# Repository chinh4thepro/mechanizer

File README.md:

## What and Why?

This is an ortholinear, split keyboard with wireless functionality and a display with a theme based on the song Mesmerizer by 32ki. I designed this keyboard to improve on issues I had with my previous ortholinear keyboard design, the blahajergo.

## Images

### Overall

### Schematic

### PCB

## BOM

| Name                                      | Qty   | Price     | Vendor        | Link                                                                              |
|-------------------------------------------|-------|-----------|---------------|-----------------------------------------------------------------------------------|
| THT 1N4148 Diodes                         | 54    | $0.00     | HackClub      | N/A                                                                               |
| KBDiy Toy                                 | 54    | $24.45    | AliExpress    | https://www.aliexpress.us/item/3256807300360436.html                              |
| JWK Linear Switches                       | 54    | $14.4     | typeractive   | https://typeractive.xyz/products/jwk-jwick-linear-switches?variant=45434593968359 |
| Kalih MX hotswap sockets                  | 54    | $13.45    | AliExpress    | https://www.aliexpress.us/item/3256808768257055.html                              |
| 4P4C jack                                 | 2     | $1.87     | AliExpress    | https://www.aliexpress.us/item/3256807699240291.html                              |
| JST connector                             | 2     | $0.73     | AliExpress    | https://www.aliexpress.us/item/3256808844534562.html                              |
| 0.91" Oled display                        | 2     | $1.96     | AliExpress    | https://www.aliexpress.us/item/3256805114690528.html                              |
| 3.7v Lithium battery                      | 2     | $8.00     | typeractive   | https://typeractive.xyz/products/lithium-battery-110mah?variant=43294731665639    |
| JST connector                             | 2     | $1.00     | typeractive   | https://typeractive.xyz/products/battery-jack?variant=45597492707559              |
| SMD side button                           | 2     | $1.50     | typeractive   | https://typeractive.xyz/products/reset-button                                     |
| SPDT Switch                               | 2     | $1.50     | typeractive   | https://typeractive.xyz/products/power-switch?variant=45597854171367              |
| M2 screws                                 | 24    | $2.44     | AliExpress    | https://www.aliexpress.us/item/2255799870438450.html                              |
| M2 standoffs                              | 12    | $5.40     | AliExpress    | https://www.aliexpress.us/item/3256806016664762.html                              |
| Seeed XIAO ESP32-S3 Plus (already own)    | 2     | $13.80    | seeedstudio   | https://www.seeedstudio.com/Seeed-Studio-XIAO-ESP32S3-Plus-p-6361.html            |
| PCB                                       | 1 (5) | $36.92    | jlcpcb        | See jlcpcb pic in Files                                                           |

| Total                                                                                                                                             |
|---------------------------------------------------------------------------------------------------------------------------------------------------|
| AliExpress: $52.83 subtotal + $4.24 shipping + $3.33 fees = $58.61 total                                                                          |
| typeractive: $26.40 subtotal + $0.00 shipping + $0.00 fees = $26.40 total                                                                         |
| seeedstudio: $0.00 subtotal + $0.00 shipping + $0.00 fees = $0.00 total                                                                           |
| jlcpcb: $21.40 subtotal + $15.52 shipping + $0.00 fees = $36.92 total                                                                             |
| Total: $121.93                                                                                                                                     |

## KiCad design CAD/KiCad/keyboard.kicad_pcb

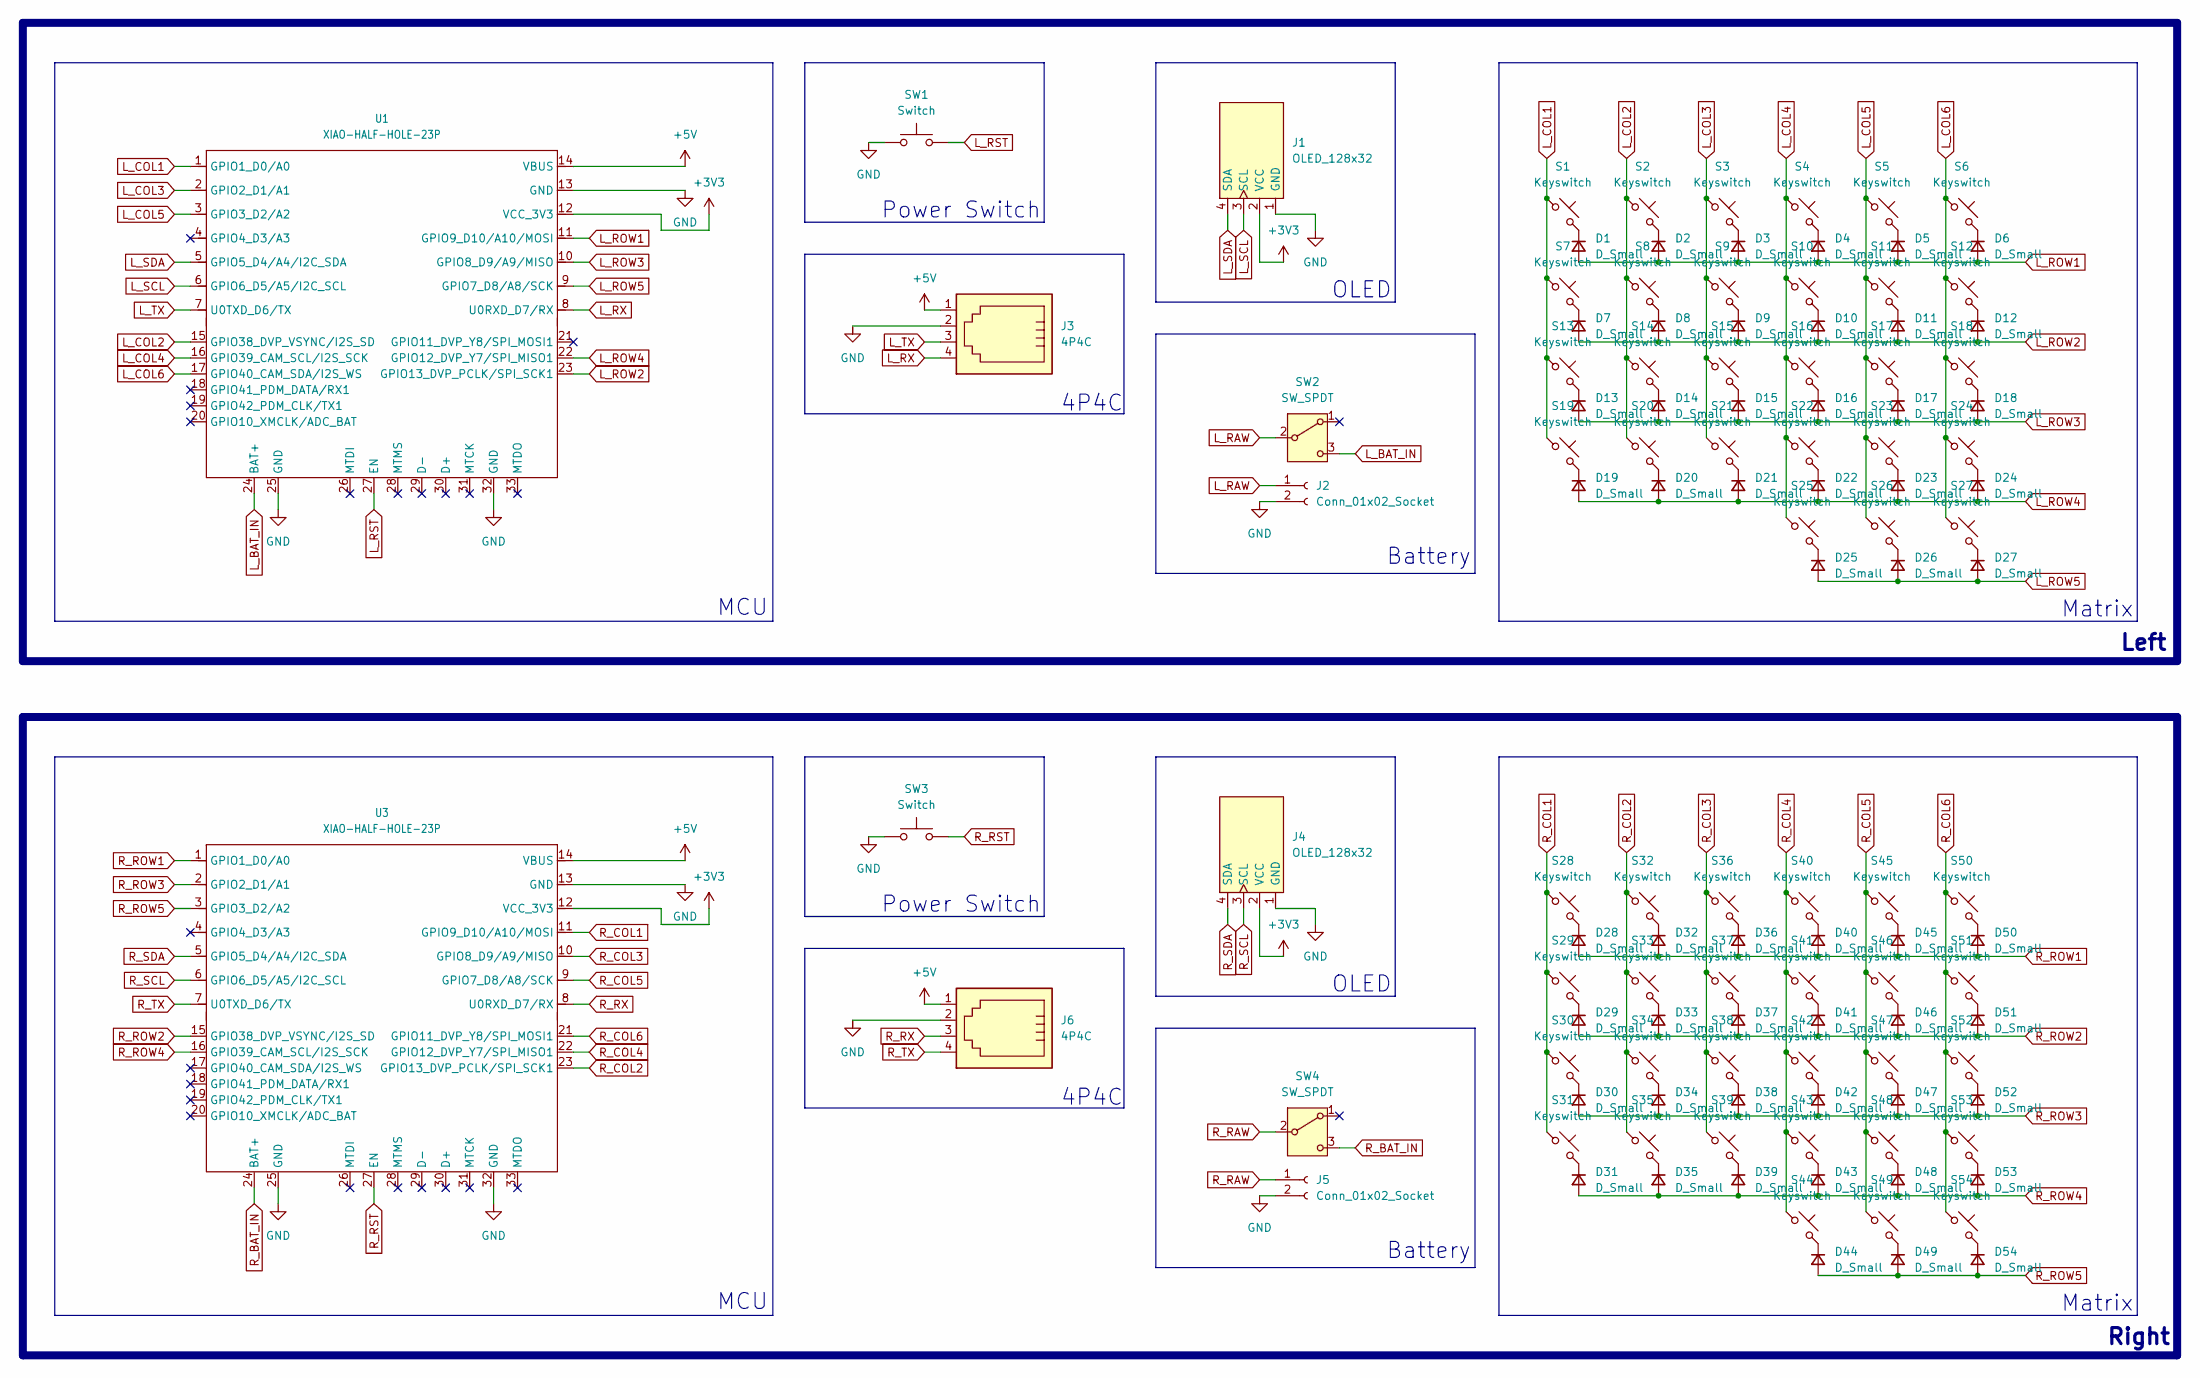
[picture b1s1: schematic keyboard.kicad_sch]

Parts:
D1, D2, D3, D4, D5, D6, D7, D8, D9, D10, D11, D12, D13, D14, D15, D16, D17, D18, D19, D20, D21, D22, D23, D24, D25, D26, D27, D28, D29, D30, D31, D32, D33, D34, D35, D36, D37, D38, D39, D40, D41, D42, D43, D44, D45, D46, D47, D48, D49, D50, D51, D52, D53, D54: D_Small; ComboDiode
J1, J4: OLED_128x32
J2, J5: Conn_01x02_Socket; JST_PH_S2B-PH-K_1x02_P2.00mm_Horizontal
J3, J6: 4P4C; RJ9_Evercom_5301-440xxx_Horizontal
S1, S2, S3, S4, S5, S6, S7, S8, S9, S10, S11, S12, S13, S14, S15, S16, S17, S18, S19, S20, S21, S22, S23, S24, S25, S26, S27, S28, S29, S30, S31, S32, S33, S34, S35, S36, S37, S38, S39, S40, S41, S42, S43, S44, S45, S46, S47, S48, S49, S50, S51, S52, S53, S54: Keyswitch; Hotswap_MX
SW1, SW3: Switch; reset_switch_smd_side
SW2, SW4: SW_SPDT; power_switch_smd_side
U1, U3: XIAO-HALF-HOLE-23P; Xiao_ESP32S3_Plus.kicad_sym

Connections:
+3V3: J1.2 (VCC), J4.2 (VCC), U1.12 (VCC_3V3), U3.12 (VCC_3V3)
+5V: J3.1, J6.1, U1.14 (VBUS), U3.14 (VBUS)
GND: J1.1 (GND), J2.2, J3.2, J4.1 (GND), J5.2, J6.2, SW1.1, SW3.1, U1.13 (GND), U1.25 (GND), U1.32 (GND), U3.13 (GND), U3.25 (GND), U3.32 (GND)
L_BAT_IN: SW2.3 (C), U1.24 (BAT+)
L_COL1: S1.1, S7.1, S13.1, S19.1, U1.1 (GPIO1_D0/A0)
L_COL2: S2.1, S8.1, S14.1, S20.1, U1.15 (GPIO38_DVP_VSYNC/I2S_SD)
L_COL3: S3.1, S9.1, S15.1, S21.1, U1.2 (GPIO2_D1/A1)
L_COL4: S4.1, S10.1, S16.1, S22.1, S25.1, U1.16 (GPIO39_CAM_SCL/I2S_SCK)
L_COL5: S5.1, S11.1, S17.1, S23.1, S26.1, U1.3 (GPIO3_D2/A2)
L_COL6: S6.1, S12.1, S18.1, S24.1, S27.1, U1.17 (GPIO40_CAM_SDA/I2S_WS)
L_RAW: J2.1, SW2.2 (B)
L_ROW1: D1.2 (A), D2.2 (A), D3.2 (A), D4.2 (A), D5.2 (A), D6.2 (A), U1.11 (GPIO9_D10/A10/MOSI)
L_ROW2: D7.2 (A), D8.2 (A), D9.2 (A), D10.2 (A), D11.2 (A), D12.2 (A), U1.23 (GPIO13_DVP_PCLK/SPI_SCK1)
L_ROW3: D13.2 (A), D14.2 (A), D15.2 (A), D16.2 (A), D17.2 (A), D18.2 (A), U1.10 (GPIO8_D9/A9/MISO)
L_ROW4: D19.2 (A), D20.2 (A), D21.2 (A), D22.2 (A), D23.2 (A), D24.2 (A), U1.22 (GPIO12_DVP_Y7/SPI_MISO1)
L_ROW5: D25.2 (A), D26.2 (A), D27.2 (A), U1.9 (GPIO7_D8/A8/SCK)
L_RST: SW1.2, U1.27 (EN)
L_RX: J3.4, U1.8 (U0RXD_D7/RX)
L_SCL: J1.3 (SCL), U1.6 (GPIO6_D5/A5/I2C_SCL)
L_SDA: J1.4 (SDA), U1.5 (GPIO5_D4/A4/I2C_SDA)
L_TX: J3.3, U1.7 (U0TXD_D6/TX)
unnamed: D1.1 (K), S1.2
unnamed: D2.1 (K), S2.2
unnamed: D3.1 (K), S3.2
unnamed: D4.1 (K), S4.2
unnamed: D5.1 (K), S5.2
unnamed: D6.1 (K), S6.2
unnamed: D7.1 (K), S7.2
unnamed: D8.1 (K), S8.2
unnamed: D9.1 (K), S9.2
unnamed: D10.1 (K), S10.2
unnamed: D11.1 (K), S11.2
unnamed: D12.1 (K), S12.2
unnamed: D13.1 (K), S13.2
unnamed: D14.1 (K), S14.2
unnamed: D15.1 (K), S15.2
unnamed: D16.1 (K), S16.2
unnamed: D17.1 (K), S17.2
unnamed: D18.1 (K), S18.2
unnamed: D19.1 (K), S19.2
unnamed: D20.1 (K), S20.2
unnamed: D21.1 (K), S21.2
unnamed: D22.1 (K), S22.2
unnamed: D23.1 (K), S23.2
unnamed: D24.1 (K), S24.2
unnamed: D25.1 (K), S25.2
unnamed: D26.1 (K), S26.2
unnamed: D27.1 (K), S27.2
unnamed: D28.1 (K), S28.2
unnamed: D29.1 (K), S29.2
unnamed: D30.1 (K), S30.2
unnamed: D31.1 (K), S31.2
unnamed: D32.1 (K), S32.2
unnamed: D33.1 (K), S33.2
unnamed: D34.1 (K), S34.2
unnamed: D35.1 (K), S35.2
unnamed: D36.1 (K), S36.2
unnamed: D37.1 (K), S37.2
unnamed: D38.1 (K), S38.2
unnamed: D39.1 (K), S39.2
unnamed: D40.1 (K), S40.2
unnamed: D41.1 (K), S41.2
unnamed: D42.1 (K), S42.2
unnamed: D43.1 (K), S43.2
unnamed: D44.1 (K), S44.2
unnamed: D45.1 (K), S45.2
unnamed: D46.1 (K), S46.2
unnamed: D47.1 (K), S47.2
unnamed: D48.1 (K), S48.2
unnamed: D49.1 (K), S49.2
unnamed: D50.1 (K), S50.2
unnamed: D51.1 (K), S51.2
unnamed: D52.1 (K), S52.2
unnamed: D53.1 (K), S53.2
unnamed: D54.1 (K), S54.2
R_BAT_IN: SW4.3 (C), U3.24 (BAT+)
R_COL1: S28.1, S29.1, S30.1, S31.1, U3.11 (GPIO9_D10/A10/MOSI)
R_COL2: S32.1, S33.1, S34.1, S35.1, U3.23 (GPIO13_DVP_PCLK/SPI_SCK1)
R_COL3: S36.1, S37.1, S38.1, S39.1, U3.10 (GPIO8_D9/A9/MISO)
R_COL4: S40.1, S41.1, S42.1, S43.1, S44.1, U3.22 (GPIO12_DVP_Y7/SPI_MISO1)
R_COL5: S45.1, S46.1, S47.1, S48.1, S49.1, U3.9 (GPIO7_D8/A8/SCK)
R_COL6: S50.1, S51.1, S52.1, S53.1, S54.1, U3.21 (GPIO11_DVP_Y8/SPI_MOSI1)
R_RAW: J5.1, SW4.2 (B)
R_ROW1: D28.2 (A), D32.2 (A), D36.2 (A), D40.2 (A), D45.2 (A), D50.2 (A), U3.1 (GPIO1_D0/A0)
R_ROW2: D29.2 (A), D33.2 (A), D37.2 (A), D41.2 (A), D46.2 (A), D51.2 (A), U3.15 (GPIO38_DVP_VSYNC/I2S_SD)
R_ROW3: D30.2 (A), D34.2 (A), D38.2 (A), D42.2 (A), D47.2 (A), D52.2 (A), U3.2 (GPIO2_D1/A1)
R_ROW4: D31.2 (A), D35.2 (A), D39.2 (A), D43.2 (A), D48.2 (A), D53.2 (A), U3.16 (GPIO39_CAM_SCL/I2S_SCK)
R_ROW5: D44.2 (A), D49.2 (A), D54.2 (A), U3.3 (GPIO3_D2/A2)
R_RST: SW3.2, U3.27 (EN)
R_RX: J6.3, U3.8 (U0RXD_D7/RX)
R_SCL: J4.3 (SCL), U3.6 (GPIO6_D5/A5/I2C_SCL)
R_SDA: J4.4 (SDA), U3.5 (GPIO5_D4/A4/I2C_SDA)
R_TX: J6.4, U3.7 (U0TXD_D6/TX)

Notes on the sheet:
Power Switch
Left
Battery
Matrix
4P4C
Right
MCU
OLED

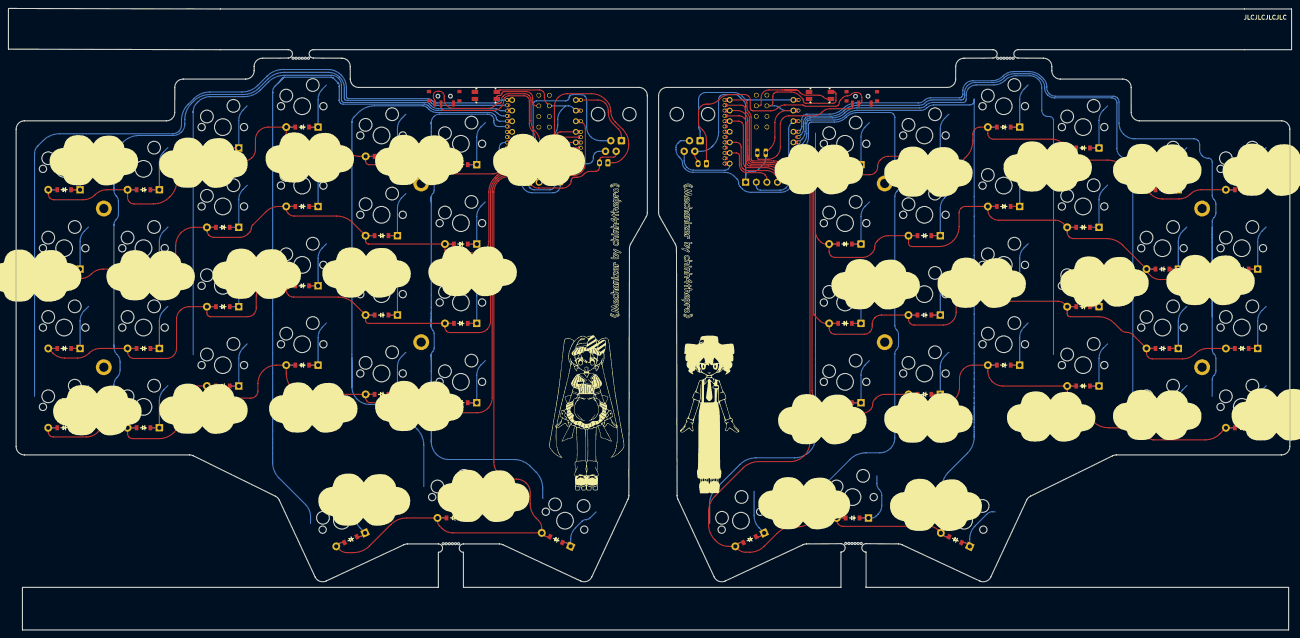
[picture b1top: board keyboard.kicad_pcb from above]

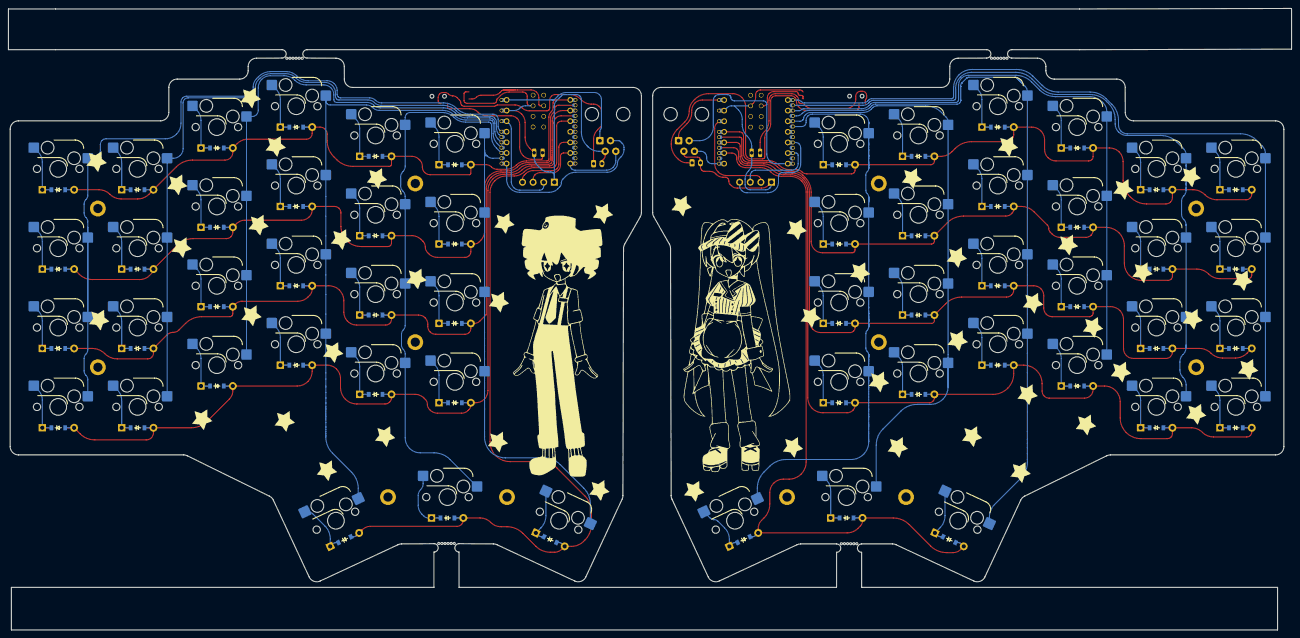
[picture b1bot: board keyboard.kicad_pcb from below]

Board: 2 copper layers, 307.2 x 148.8 mm, 132 parts (2 on the bottom side), 93 nets.

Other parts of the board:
H1, H2, H3, H4, H5, H6, H7, H8, H9, H10, H11, H12: mounting_hole_plated

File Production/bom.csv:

Designator,Footprint,Quantity,Value,LCSC Part #
"D1, D10, D11, D12, D13, D14, D15, D16, D17, D18, D19, D2, D20, D21, D22, D23, D24, D25, D26, D27, D28, D29, D3, D30, D31, D32, D33, D34, D35, D36, D37, D38, D39, D4, D40, D41, D42, D43, D44, D45, D46, D47, D48, D49, D5, D50, D51, D52, D53, D54, D6, D7, D8, D9",ComboDiode,54,D_Small,
"H1, H10, H11, H12, H2, H3, H4, H5, H6, H7, H8, H9",mounting_hole_plated,12,,
"J1, J4",OLED_128x32,2,OLED_128x32,
"J2, J5",JST_PH_S2B-PH-K_1x02_P2.00mm_Horizontal,2,Conn_01x02_Socket,
"J3, J6",RJ9_Evercom_5301-440xxx_Horizontal,2,4P4C,
"S1, S10, S11, S12, S13, S14, S15, S16, S17, S18, S19, S2, S20, S21, S22, S23, S24, S25, S26, S27, S28, S29, S3, S30, S31, S32, S33, S34, S35, S36, S37, S38, S39, S4, S40, S41, S42, S43, S44, S45, S46, S47, S48, S49, S5, S50, S51, S52, S53, S54, S6, S7, S8, S9",Hotswap_MX,54,Keyswitch,
"SW1, SW3",reset_switch_smd_side,2,Switch,
"SW2, SW4",power_switch_smd_side,2,SW_SPDT,
"U1, U3",Xiao_ESP32S3_Plus.kicad_sym,2,XIAO-HALF-HOLE-23P,

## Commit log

2025-03-02 kicad
2025-03-20 schematic
2025-03-20 cleanup
2025-04-22 mousebites
2025-06-07 partially update
2025-06-07 partially update pt2
2025-06-07 partial readme
2025-06-07 complete images
2025-06-07 update images
2025-06-07 redo mousebites cause i forgor
2025-06-08 stuff...
2025-06-09 cad files
2025-06-11 reroute for full duplex split functionality
2025-06-11 firmware
2025-06-11 update the gitignore
2025-06-11 bom in csv format
2025-06-11 overall image
2025-06-11 production files
2025-06-11 im too used to java
2025-06-11 update BOM
2025-06-11 oops
2025-10-06 i forgor the step files
2025-10-07 add pcb to bom
2025-10-09 move production directory
